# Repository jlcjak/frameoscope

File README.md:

# frameoscope
oscilloscope expansion card / module for framework laptops 

[frame.fasterscope.com](https://frame.fasterscope.com)

## Tech Specs
- sampling rate: 40MSPS
- bandwidth: 10MHz
- resolution: 8bit
- interface: usb2
- front end Rin: 8.5KOhm
- front end Cin: ~5pF
- input voltage: 0-5V (protected from reverse and high voltage)

## How to use
I have built and tested frameoscope, it works! I made it compatible with ngscopeclient.
Here is how to use it:
1. install [ngscopeclient](https://github.com/ngscopeclient/scopehal-apps/releases/)
2. plug in frameoscope and run: `curl -fsSL frame.fasterscope.com/install.sh | bash` (Source code in "/software")

That's it, now ngscopeclient should see frameoscope as an oscilloscope

to uninstall: `curl -fsSL frame.fasterscope.com/uninstall.sh | bash`

this works on ubuntu 24, for other distros clone this repo and ask codex(/your agent of choice) to make it work

The script installs, starts and enables a service that will flash frameoscope upon insertion
and start a bridge that translates the stream into ngscopeclient compatible packets

## Remarks
- The board is mainly comprimized of a TI adc, an iCE40 fpga and a usb PHY (FT232H).
- The fpga is used as an protocol tranlator between the busses on the usb PHY and adc.
- You can program the fpga directly over usb, through FT232H.
- There is no flash on the fpga so you need to reprogram it on reset or use iCE nvcm

## manufacturing
- all components are sourcable from lcsc, for easy assembly in china.
- use a 0.8mm board so you can solder on the usb connector

Nextpcb sponsored the first iteration of this project, thanks nextpcb. you can easily use them to make this for very cheap. They are professional, fast and cheap. [nextpcb.com](https://www.nextpcb.com/?code=Jak)

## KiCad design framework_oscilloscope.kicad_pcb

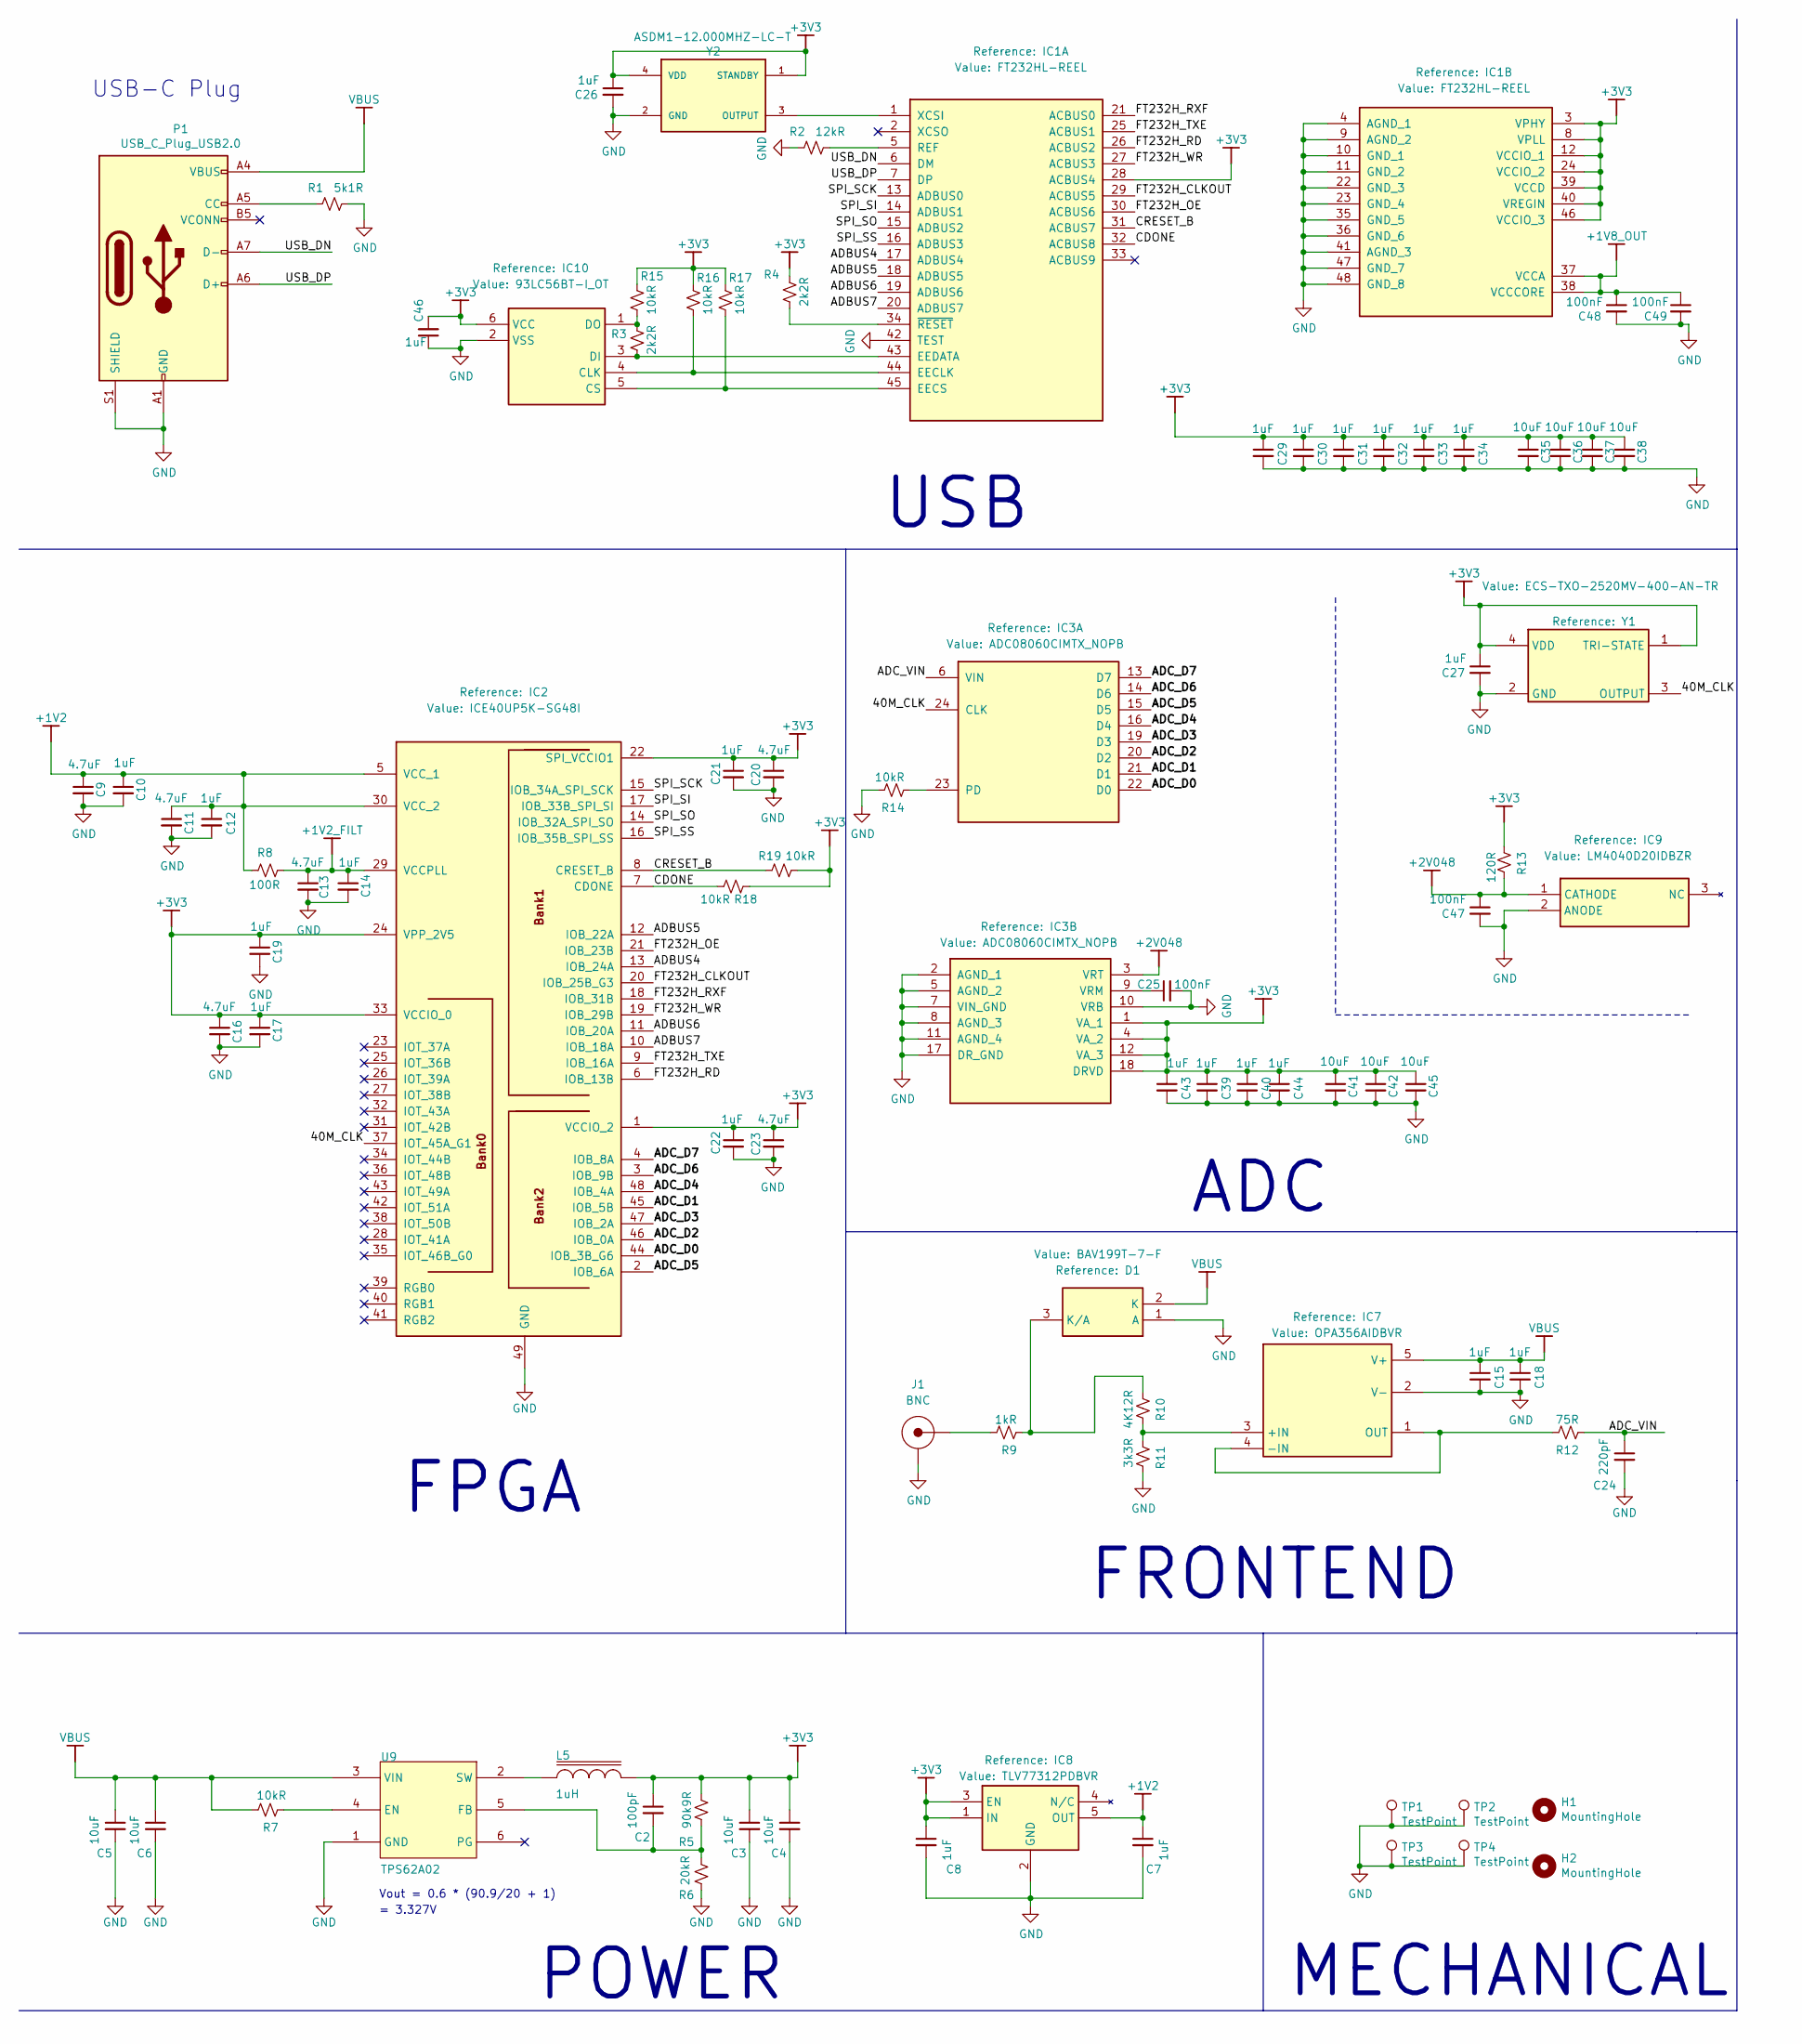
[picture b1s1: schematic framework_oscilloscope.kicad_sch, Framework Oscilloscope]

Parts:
C2: 100pF; 0402_1005Metric_CAP; MANUFACTURER PART NUMBER CC0402JRNPO9BN101
C3, C4, C5, C6, C35, C36, C37, C38, C41, C42, C45: 10uF; 0603_1608Metric_CAP; MANUFACTURER PART NUMBER CL10A106MQ8NNNC
C7, C8, C10, C12, C14, C15, C17, C18, C19, C21, C22, C26, C27, C29, C30, C31, C32, C33, C34, C39, C40, C43, C44, C46: 1uF; 0402_1005Metric_CAP; MANUFACTURER PART NUMBER CL05A105KO5NNNC
C9, C11, C13, C16, C20, C23: 4.7uF; 0603_1608Metric_CAP; MANUFACTURER PART NUMBER CL10A475KP8NNNC
C24: 220pF; 0402_1005Metric_CAP; MANUFACTURER PART NUMBER CC0402JRNPO9BN221
C25, C47, C48, C49: 100nF; 0402_1005Metric_CAP; MANUFACTURER PART NUMBER CL05B104KO5NNNC
D1: BAV199T-7-F; SOT50P160X90-3N; MANUFACTURER PART NUMBER BAV199T-7-F
H1, H2: MountingHole; MountingHole_2.2mm_M2
IC1: FT232HL-REEL; QFP50P900X900X160-48N; MANUFACTURER PART NUMBER FT232HL-REEL
IC2: ICE40UP5K-SG48I; QFN50P700X700X100-49N-D; MANUFACTURER PART NUMBER ICE40UP5K-SG48I
IC3: ADC08060CIMTX_NOPB; SOP65P640X120-24N; MANUFACTURER PART NUMBER ADC08060CIMTX/NOPB
IC7: OPA356AIDBVR; SOT95P280X145-5N; MANUFACTURER PART NUMBER OPA356AIDBVR
IC8: TLV77312PDBVR; SOT95P280X145-5N; MANUFACTURER PART NUMBER TLV77312PDBVR
IC9: LM4040D20IDBZR; SOT95P237X112-3N; MANUFACTURER PART NUMBER LM4040D20IDBZR
IC10: 93LC56BT-I_OT; SOT95P270X145-6N; MANUFACTURER PART NUMBER 93LC56BT-I/OT
J1: BNC; MOL_0731000105; MANUFACTURER PART NUMBER 73100-0105
L5: 1uH; 1210_3225Metric; MANUFACTURER PART NUMBER SRP3212-1R0M
P1: USB_C_Plug_USB2.0; USB_C_Plug_Molex_105444; MANUFACTURER PART NUMBER 105444-0001
R1: 5k1R; 0402_1005Metric; MANUFACTURER PART NUMBER RC0402FR-075K1L
R2: 12kR; 0402_1005Metric; MANUFACTURER PART NUMBER ERA2AEB123X
R3, R4: 2k2R; 0402_1005Metric; MANUFACTURER PART NUMBER RC0402JR-072K2L
R5: 90k9R; 0402_1005Metric; MANUFACTURER PART NUMBER RC0402FR-0790K9L
R6: 20kR; 0402_1005Metric; MANUFACTURER PART NUMBER RC0402FR-0720KL
R7, R14, R15, R16, R17, R18, R19: 10kR; 0402_1005Metric; MANUFACTURER PART NUMBER RC0402JR-0710KL
R8: 100R; 0402_1005Metric; MANUFACTURER PART NUMBER RC0402FR-07100RL
R9: 1kR; 0402_1005Metric; MANUFACTURER PART NUMBER RT0402FRE071KL
R10: 4K12R; 0402_1005Metric; MANUFACTURER PART NUMBER RT0402BRD074K12L
R11: 3k3R; 0402_1005Metric; MANUFACTURER PART NUMBER RT0402BRD073K3L
R12: 75R; 0402_1005Metric; MANUFACTURER PART NUMBER RC0402FR-0775RL
R13: 120R; 0402_1005Metric; MANUFACTURER PART NUMBER RC0402FR-0775RL
TP1, TP2, TP3, TP4: TestPoint; TestPoint_Pad_1.5x1.5mm
U9: TPS62A02; TI_SOT563_DRL0006A; MANUFACTURER PART NUMBER TPS62A02DRLR
Y1: ECS-TXO-2520MV-400-AN-TR; ECSTXO252033250ANTR; MANUFACTURER PART NUMBER ECS-TXO-2520MV-400-AN-TR
Y2: ASDM1-12.000MHZ-LC-T; XTAL_ASDM1-12.000MHZ-LC-T; MANUFACTURER PART NUMBER ASDM1-12.000MHZ-LC-T

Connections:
+1V2: C7.1, C9.1, C10.1, C11.1, C12.1, IC2.5 (VCC_1), IC2.30 (VCC_2), IC8.5 (OUT), R8.2
+1V2_FILT: C13.1, C14.1, IC2.29 (VCCPLL), R8.1
+1V8_OUT: C48.1, C49.1, IC1.37 (VCCA), IC1.38 (VCCCORE)
+2V048: C47.1, IC3.3 (VRT), IC9.1 (CATHODE), R13.1
+3V3: C2.1, C3.1, C4.1, C8.1, C16.1, C17.1, C19.1, C20.1, C21.1, C22.1, C23.1, C26.1, C27.1, C29.1, C30.1, C31.1, C32.1, C33.1, C34.1, C35.1, C36.1, C37.1, C38.1, C39.1, C40.1, C41.1, C42.1, C43.1, C44.1, C45.1, C46.2, IC1.3 (VPHY), IC1.8 (VPLL), IC1.12 (VCCIO_1), IC1.24 (VCCIO_2), IC1.28 (ACBUS4), IC1.39 (VCCD), IC1.40 (VREGIN), IC1.46 (VCCIO_3), IC2.1 (VCCIO_2), IC2.22 (SPI_VCCIO1), IC2.24 (VPP_2V5), IC2.33 (VCCIO_0), IC3.1 (VA_1), IC3.4 (VA_2), IC3.12 (VA_3), IC3.18 (DRVD), IC8.1 (IN), IC8.3 (EN), IC10.6 (VCC), L5.2, R4.2, R5.2, R13.2, R15.2, R16.2, R17.2, R18.1, R19.1, Y1.1 (TRI-STATE), Y1.4 (VDD), Y2.1 (STANDBY), Y2.4 (VDD)
/40M_CLK: IC2.37 (IOT_45A_G1), IC3.24 (CLK), Y1.3 (OUTPUT)
/ADBUS4: IC1.17 (ADBUS4), IC2.13 (IOB_24A)
/ADBUS5: IC1.18 (ADBUS5), IC2.12 (IOB_22A)
/ADBUS6: IC1.19 (ADBUS6), IC2.11 (IOB_20A)
/ADBUS7: IC1.20 (ADBUS7), IC2.10 (IOB_18A)
/ADC_D0: IC2.44 (IOB_3B_G6), IC3.22 (D0)
/ADC_D1: IC2.45 (IOB_5B), IC3.21 (D1)
/ADC_D2: IC2.46 (IOB_0A), IC3.20 (D2)
/ADC_D3: IC2.47 (IOB_2A), IC3.19 (D3)
/ADC_D4: IC2.48 (IOB_4A), IC3.16 (D4)
/ADC_D5: IC2.2 (IOB_6A), IC3.15 (D5)
/ADC_D6: IC2.3 (IOB_9B), IC3.14 (D6)
/ADC_D7: IC2.4 (IOB_8A), IC3.13 (D7)
/ADC_VIN: C24.1, IC3.6 (VIN), R12.2
/CDONE: IC1.32 (ACBUS8), IC2.7 (CDONE), R18.2
/CRESET_B: IC1.31 (ACBUS7), IC2.8 (CRESET_B), R19.2
/FT232H_CLKOUT: IC1.29 (ACBUS5), IC2.20 (IOB_25B_G3)
/FT232H_OE: IC1.30 (ACBUS6), IC2.21 (IOB_23B)
/FT232H_RD: IC1.26 (ACBUS2), IC2.6 (IOB_13B)
/FT232H_RXF: IC1.21 (ACBUS0), IC2.18 (IOB_31B)
/FT232H_TXE: IC1.25 (ACBUS1), IC2.9 (IOB_16A)
/FT232H_WR: IC1.27 (ACBUS3), IC2.19 (IOB_29B)
/SPI_SCK: IC1.13 (ADBUS0), IC2.15 (IOB_34A_SPI_SCK)
/SPI_SI: IC1.14 (ADBUS1), IC2.17 (IOB_33B_SPI_SI)
/SPI_SO: IC1.15 (ADBUS2), IC2.14 (IOB_32A_SPI_SO)
/SPI_SS: IC1.16 (ADBUS3), IC2.16 (IOB_35B_SPI_SS)
/USB_DN: IC1.6 (DM), P1.A7 (D-)
/USB_DP: IC1.7 (DP), P1.A6 (D+)
GND: C3.2, C4.2, C5.2, C6.2, C7.2, C8.2, C9.2, C10.2, C11.2, C12.2, C13.2, C14.2, C15.2, C16.2, C17.2, C18.2, C19.2, C20.2, C21.2, C22.2, C23.2, C24.2, C25.2, C26.2, C27.2, C29.2, C30.2, C31.2, C32.2, C33.2, C34.2, C35.2, C36.2, C37.2, C38.2, C39.2, C40.2, C41.2, C42.2, C43.2, C44.2, C45.2, C46.1, C47.2, C48.2, C49.2, D1.1 (A), IC1.4 (AGND_1), IC1.9 (AGND_2), IC1.10 (GND_1), IC1.11 (GND_2), IC1.22 (GND_3), IC1.23 (GND_4), IC1.35 (GND_5), IC1.36 (GND_6), IC1.41 (AGND_3), IC1.42 (TEST), IC1.47 (GND_7), IC1.48 (GND_8), IC2.49 (GND), IC3.2 (AGND_1), IC3.5 (AGND_2), IC3.7 (VIN_GND), IC3.8 (AGND_3), IC3.10 (VRB), IC3.11 (AGND_4), IC3.17 (DR_GND), IC7.2 (V-), IC8.2 (GND), IC9.2 (ANODE), IC10.2 (VSS), J1.2 (SHIELD), P1.A1 (GND), P1.A12 (GND), P1.B1 (GND), P1.B12 (GND), P1.S1 (SHIELD), R1.2, R2.1, R6.1, R11.1, R14.1, TP1.1 (1_1), TP2.1 (1_1), TP3.1 (1_1), TP4.1 (1_1), U9.1 (GND), Y1.2 (GND), Y2.2 (GND)
unnamed: D1.3 (K/A), R9.2, R10.2
unnamed: IC1.5 (REF), R2.2
unnamed: IC1.1 (XCSI), Y2.3 (OUTPUT)
unnamed: IC1.34 (~RESET), R4.1
unnamed: IC3.23 (PD), R14.2
unnamed: C25.1, IC3.9 (VRM)
unnamed: IC7.3 (+IN), R10.1, R11.2
unnamed: IC7.1 (OUT), IC7.4 (-IN), R12.1
unnamed: IC1.44 (EECLK), IC10.4 (CLK), R16.1
unnamed: IC1.45 (EECS), IC10.5 (CS), R17.1
unnamed: IC1.43 (EEDATA), IC10.3 (DI), R3.1
unnamed: IC10.1 (DO), R3.2, R15.1
unnamed: J1.1 (Signal), R9.1
unnamed: P1.A5 (CC), R1.1
unnamed: R7.2, U9.4 (EN)
unnamed: C2.2, R5.1, R6.2, U9.5 (FB)
unnamed: L5.1, U9.2 (SW)
VBUS: C5.1, C6.1, C15.1, C18.1, D1.2 (K), IC7.5 (V+), P1.A4 (VBUS), P1.A9 (VBUS), P1.B4 (VBUS), P1.B9 (VBUS), R7.1, U9.3 (VIN)

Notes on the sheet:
USB-C Plug
Vout = 0.6 * (90.9/20 + 1)
USB
= 3.327V
FRONTEND
ADC
MECHANICAL
POWER
FPGA

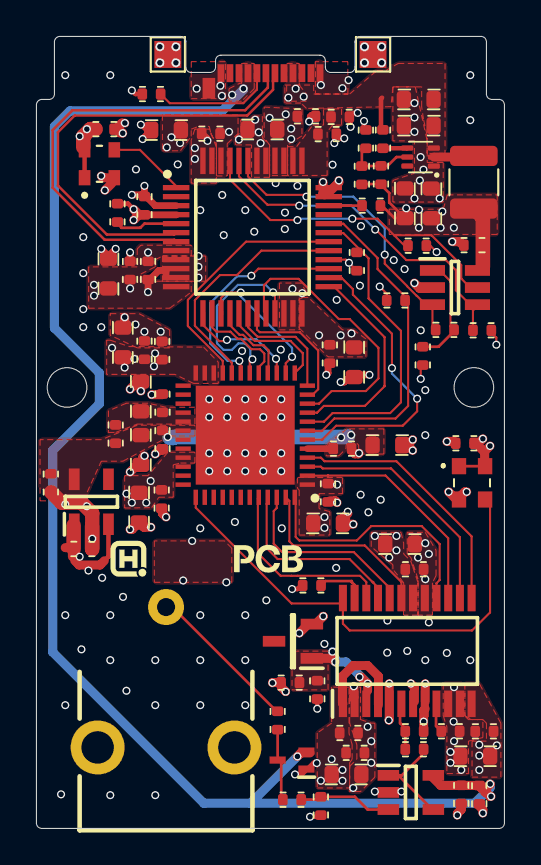
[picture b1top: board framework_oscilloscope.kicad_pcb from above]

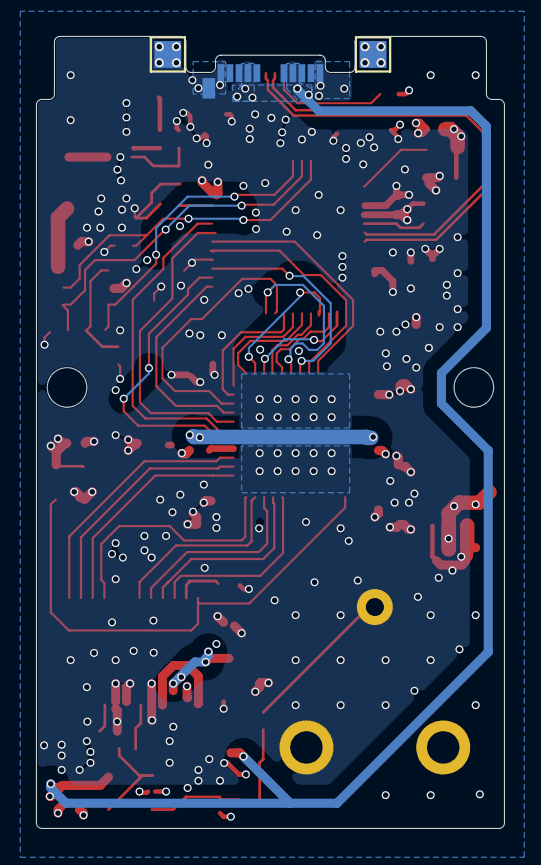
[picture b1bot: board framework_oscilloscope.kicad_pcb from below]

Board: 4 copper layers, 26.0 x 44.0 mm, 87 parts (2 on the bottom side), 52 nets.

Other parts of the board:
LOGO1: NextPCB

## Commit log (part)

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2026-05-02 gitinit
2026-05-02 cleaned up layout layers
2026-05-02 cleaned up schematics
2026-05-02 cleanup, and a little routing
2026-05-02 small sch tweek, almost done routing
2026-05-02 done routing
2026-05-02 fixed emc errors, fixed drc errors
2026-05-02 changed layout frame size
2026-05-02 added pull ups to eeprom->ftdi spi, as per reference design (tri state pins on FT232 SPI)
2026-05-02 changed stackup name to a similar 0.8mm one
2026-05-03 updated frameoscope_3d.png
2026-05-03 removed frameoscope_3d.png
2026-05-03 readded frameoscope_3d.png
2026-05-03 added frameoscdope_render.png
2026-05-03 added pictures for README
2026-05-03 updated 3d image
2026-05-04 fixed FT232-FPGA connections
2026-05-04 updated frameoscope_schematic.png
2026-05-04 changed front end bandwidth limit
2026-05-09 added part numbers for passives
2026-05-10 improved dfm
2026-06-21 added software
2026-06-21 Update README with usage instructions for frameoscope
2026-06-21 Update README to specify Ubuntu 24 compatibility
2026-06-21 Fix uninstall script URL in README
2026-06-23 updated software to only flashed tagged devices
